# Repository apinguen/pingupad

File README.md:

A hackpad with 16 buttons, an OLED screen, and an LED bar intended to be used as a Hackpad.
Onshape: https://cad.onshape.com/documents/17214055c25b4c4edecabb37/w/d13b70b86df991b167aecbf5/e/80d1be217be8b2c73be55550

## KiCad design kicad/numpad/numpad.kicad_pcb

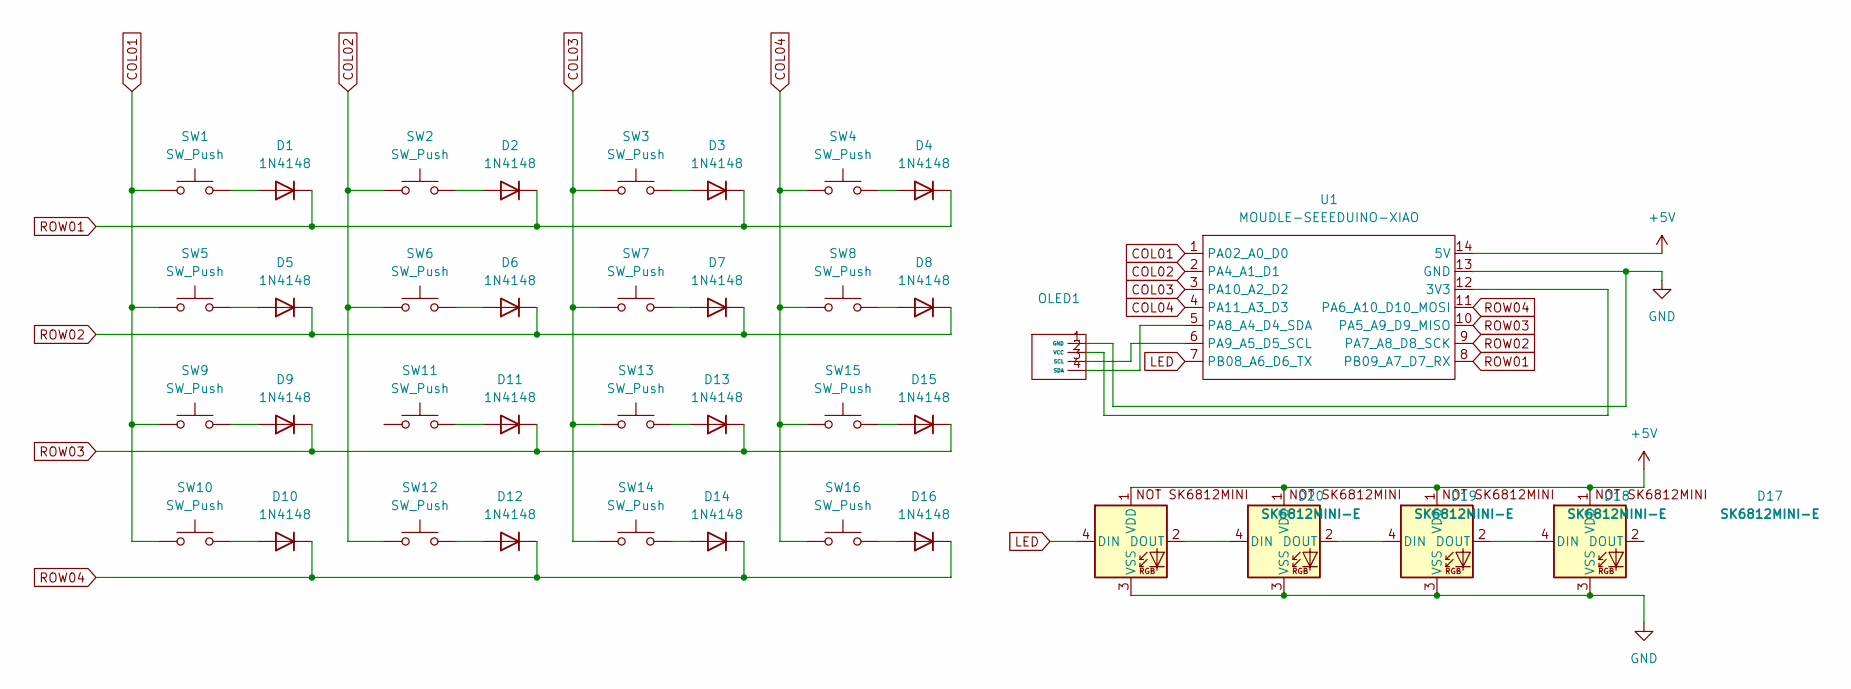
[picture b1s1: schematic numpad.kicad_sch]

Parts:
D1, D2, D3, D4, D5, D6, D7, D8, D9, D10, D11, D12, D13, D14, D15, D16: 1N4148; D_DO-35_SOD27_P7.62mm_Horizontal
D17, D18, D19, D20: SK6812MINI-E; SK6812MINI-E_fixed
OLED1: SSD1306-0.91-OLED-4pin-128x32
SW1, SW2, SW3, SW4, SW5, SW6, SW7, SW8, SW9, SW10, SW11, SW12, SW13, SW14, SW15, SW16: SW_Push; SW_Cherry_MX_1.00u_PCB
U1: MOUDLE-SEEEDUINO-XIAO; XIAO-Generic-Hybrid-14P-2.54-21X17.8MM

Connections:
+5V: D17.1 (VDD), D18.1 (VDD), D19.1 (VDD), D20.1 (VDD), U1.14 (5V)
COL01: SW1.1, SW5.1, SW9.1, SW10.1, U1.1 (PA02_A0_D0)
COL02: SW2.1, SW6.1, SW12.1, U1.2 (PA4_A1_D1)
COL03: SW3.1, SW7.1, SW13.1, SW14.1, U1.3 (PA10_A2_D2)
COL04: SW4.1, SW8.1, SW15.1, SW16.1, U1.4 (PA11_A3_D3)
GND: D17.3 (VSS), D18.3 (VSS), D19.3 (VSS), D20.3 (VSS), OLED1.1 (GND), U1.13 (GND)
LED: D20.4 (DIN), U1.7 (PB08_A6_D6_TX)
unnamed: D1.2 (A), SW1.2
unnamed: D2.2 (A), SW2.2
unnamed: D3.2 (A), SW3.2
unnamed: D4.2 (A), SW4.2
unnamed: D5.2 (A), SW5.2
unnamed: D6.2 (A), SW6.2
unnamed: D7.2 (A), SW7.2
unnamed: D8.2 (A), SW8.2
unnamed: D9.2 (A), SW9.2
unnamed: D10.2 (A), SW10.2
unnamed: D11.2 (A), SW11.2
unnamed: D12.2 (A), SW12.2
unnamed: D13.2 (A), SW13.2
unnamed: D14.2 (A), SW14.2
unnamed: D15.2 (A), SW15.2
unnamed: D16.2 (A), SW16.2
unnamed: D17.4 (DIN), D18.2 (DOUT)
unnamed: D18.4 (DIN), D19.2 (DOUT)
unnamed: D19.4 (DIN), D20.2 (DOUT)
unnamed: OLED1.3 (SCL), U1.6 (PA9_A5_D5_SCL)
unnamed: OLED1.4 (SDA), U1.5 (PA8_A4_D4_SDA)
unnamed: OLED1.2 (VCC), U1.12 (3V3)
ROW01: D1.1 (K), D2.1 (K), D3.1 (K), D4.1 (K), U1.8 (PB09_A7_D7_RX)
ROW02: D5.1 (K), D6.1 (K), D7.1 (K), D8.1 (K), U1.9 (PA7_A8_D8_SCK)
ROW03: D9.1 (K), D11.1 (K), D13.1 (K), D15.1 (K), U1.10 (PA5_A9_D9_MISO)
ROW04: D10.1 (K), D12.1 (K), D14.1 (K), D16.1 (K), U1.11 (PA6_A10_D10_MOSI)

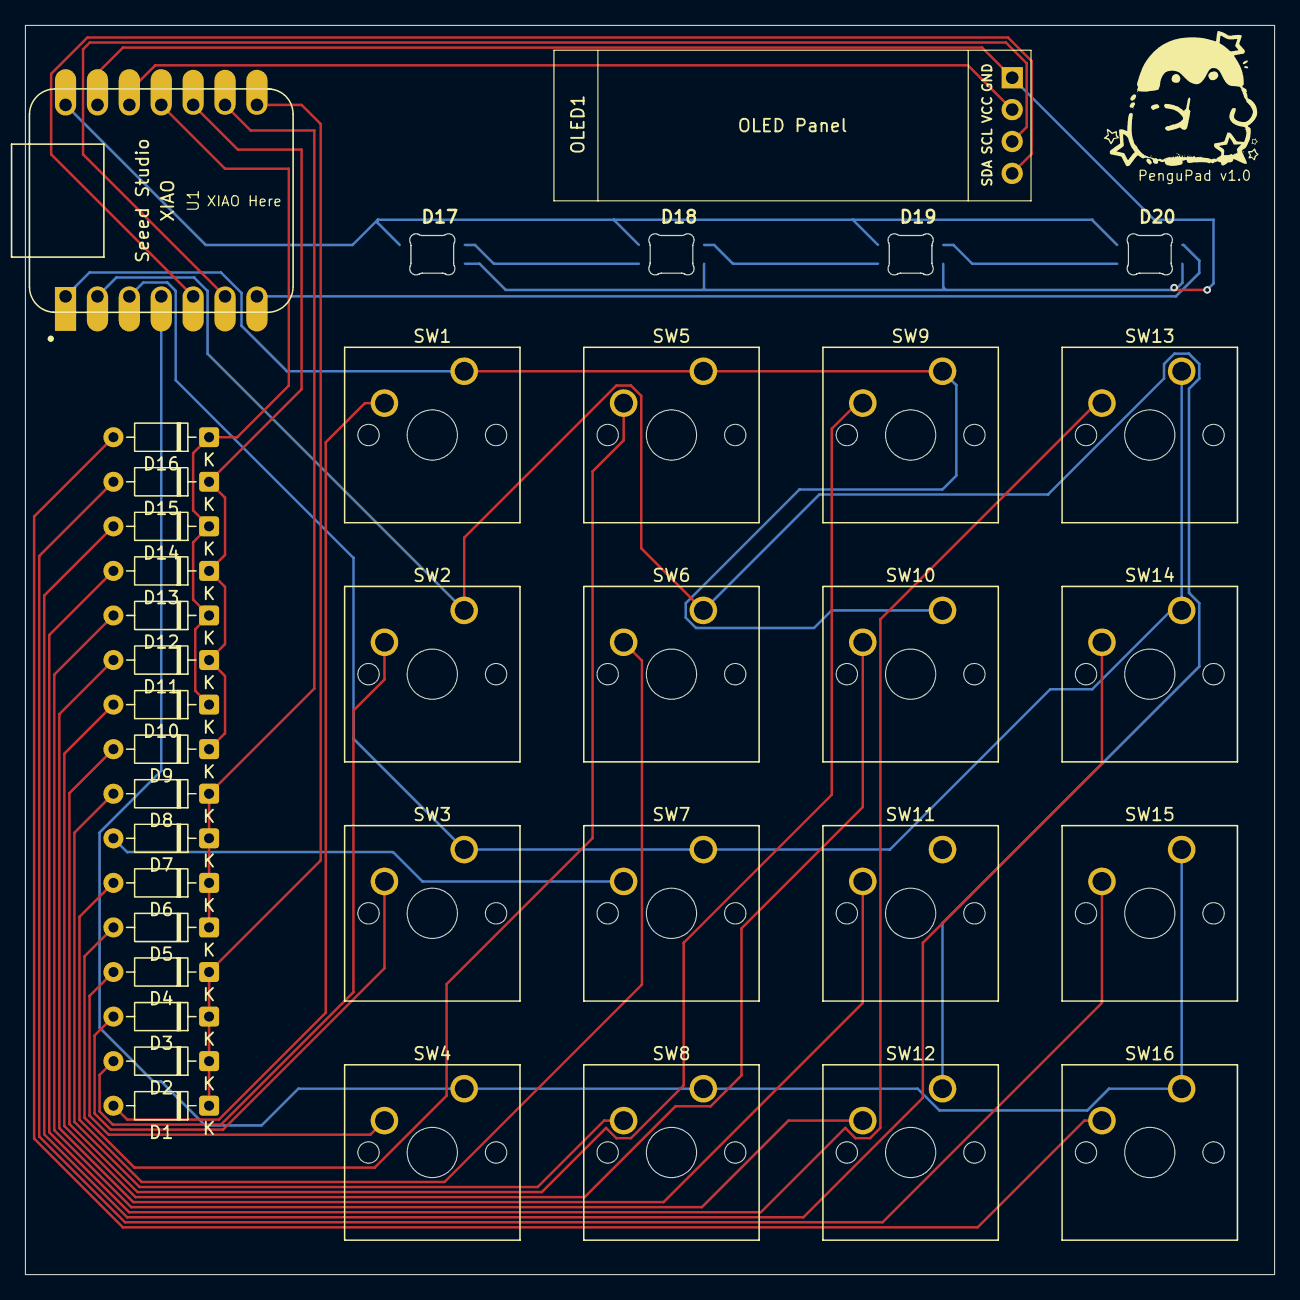
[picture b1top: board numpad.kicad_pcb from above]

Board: 2 copper layers, 99.5 x 99.5 mm, 39 parts (0 on the bottom side), 33 nets.

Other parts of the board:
G*: LOGO

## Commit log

2026-01-17 Cad files
2026-01-17 CAD link
2026-01-17 Readme
2026-01-17 firmware
